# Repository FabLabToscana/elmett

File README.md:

# elmett
Hazard monitoring and location tracking  in dangerous environments

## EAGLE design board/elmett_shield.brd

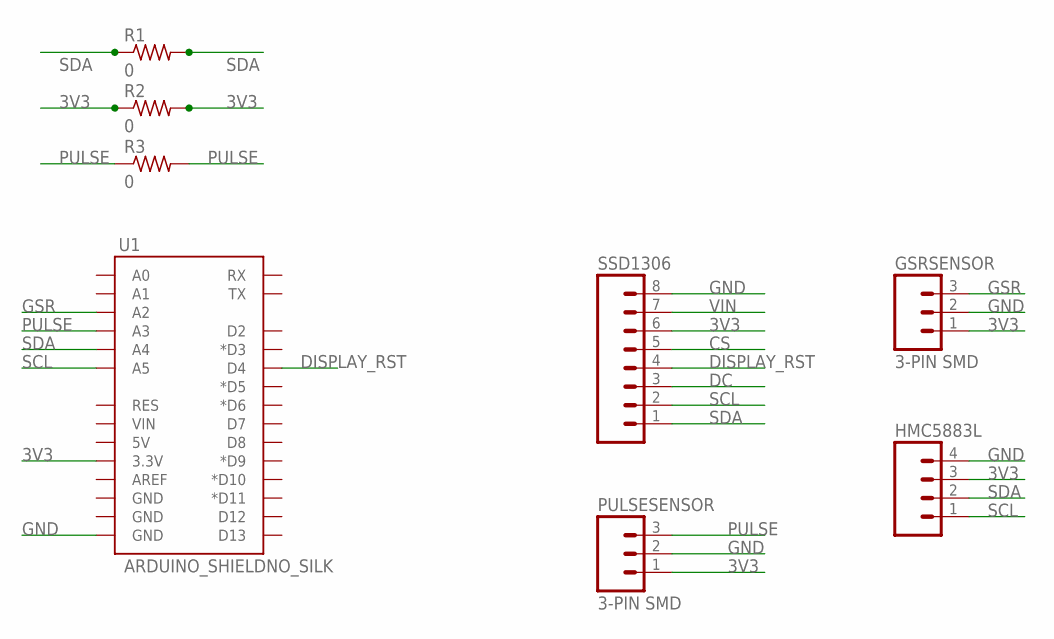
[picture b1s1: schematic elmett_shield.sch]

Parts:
GSRSENSOR: 3-PIN SMD; JST-3-SMD
HMC5883L: M04PTH; 1X04
PULSESENSOR: 3-PIN SMD; JST-3-SMD
R1, R2, R3: 0; 1206
SSD1306: M08; 1X08_ROUND
U1: ARDUINO_SHIELDNO_SILK; DUEMILANOVE_VIAS

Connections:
3V3: GSRSENSOR.1, HMC5883L.3, PULSESENSOR.1, R2.1, R2.2, SSD1306.6, U1.3.3V
CS: SSD1306.5
DC: SSD1306.3
DISPLAY_RST: SSD1306.4, U1.D4
GND: GSRSENSOR.2, HMC5883L.4, PULSESENSOR.2, SSD1306.8, U1.GND@0 (GND)
GSR: GSRSENSOR.3, U1.A2
PULSE: PULSESENSOR.3, R3.1, R3.2, U1.A3
SCL: HMC5883L.1, SSD1306.2, U1.A5
SDA: HMC5883L.2, R1.1, R1.2, SSD1306.1, U1.A4
VIN: SSD1306.7

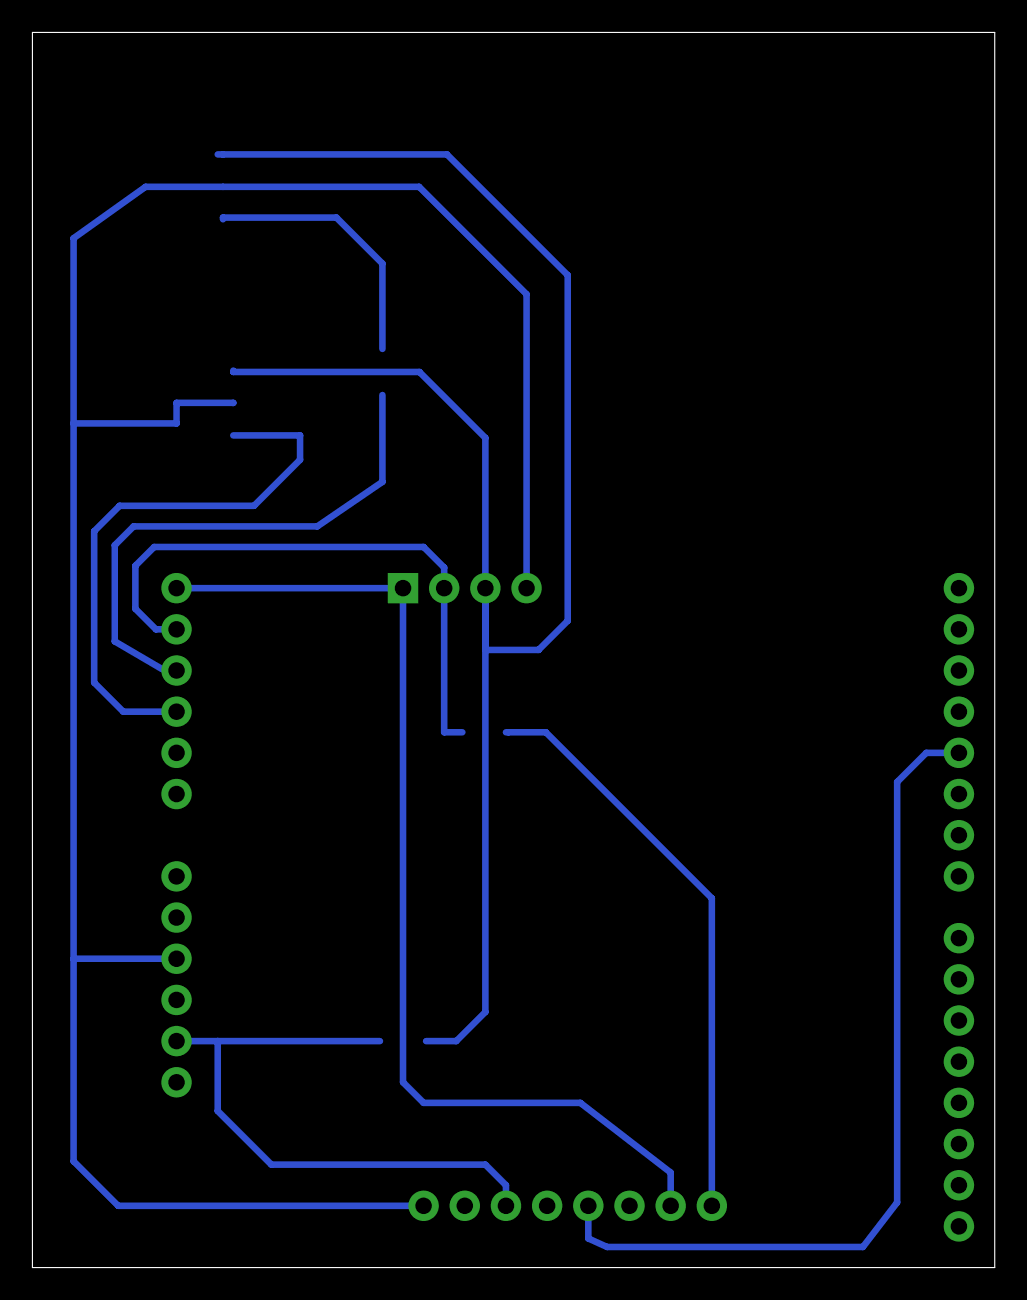
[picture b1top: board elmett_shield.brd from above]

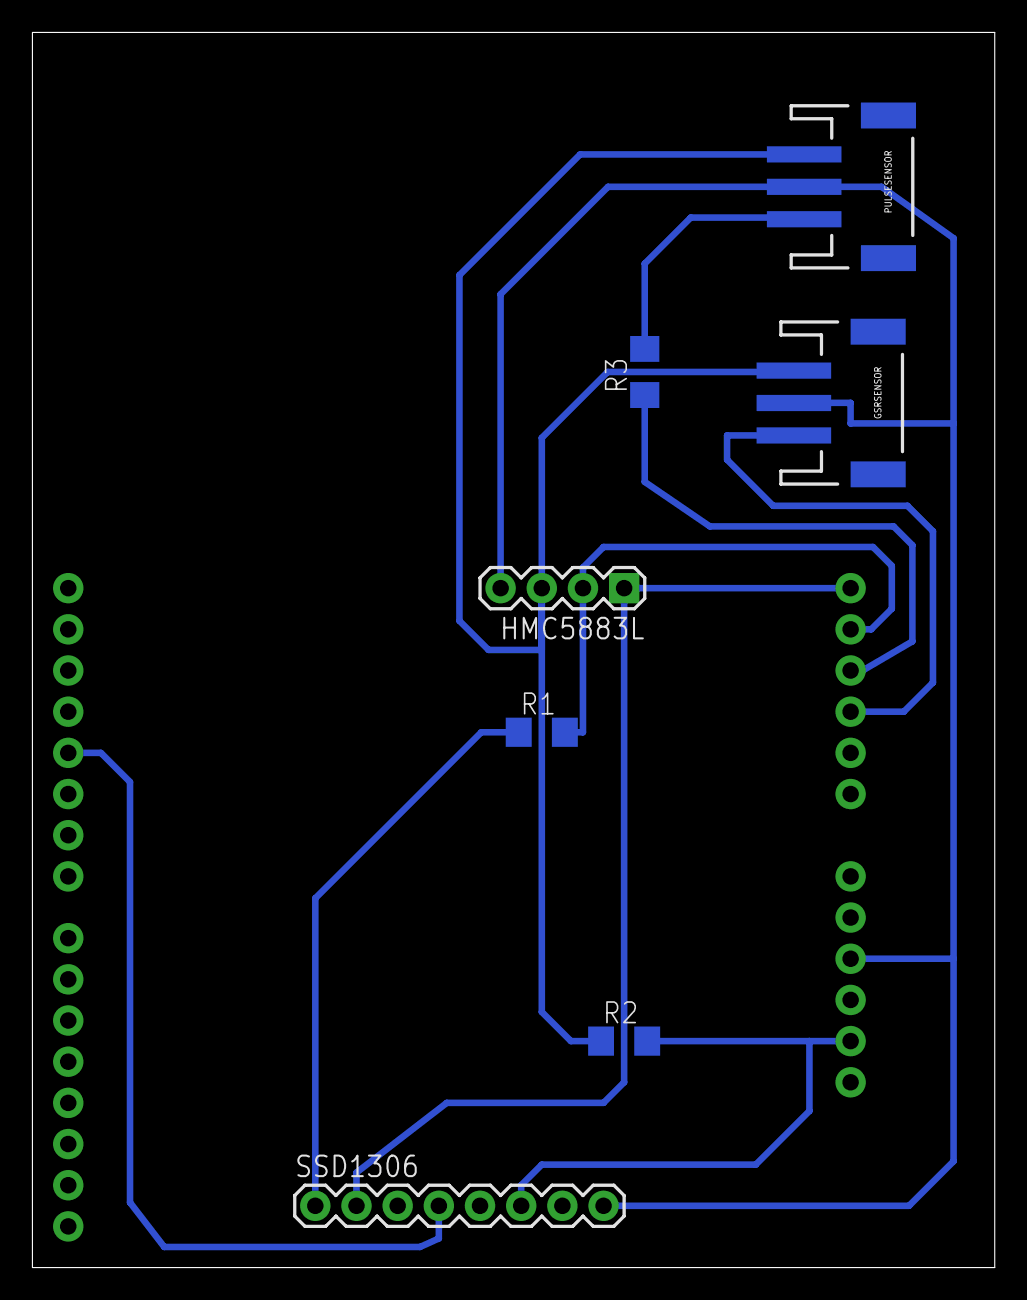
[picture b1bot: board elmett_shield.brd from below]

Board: 2 copper layers, 59.4 x 76.2 mm, 8 parts (8 on the bottom side), 7 nets.

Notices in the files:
parts and their libraries:
SparkFun-Boards: Licensing: Creative Commons ShareAlike 4.0 International - https://creativecommons.org/licenses/by-sa/4.0
